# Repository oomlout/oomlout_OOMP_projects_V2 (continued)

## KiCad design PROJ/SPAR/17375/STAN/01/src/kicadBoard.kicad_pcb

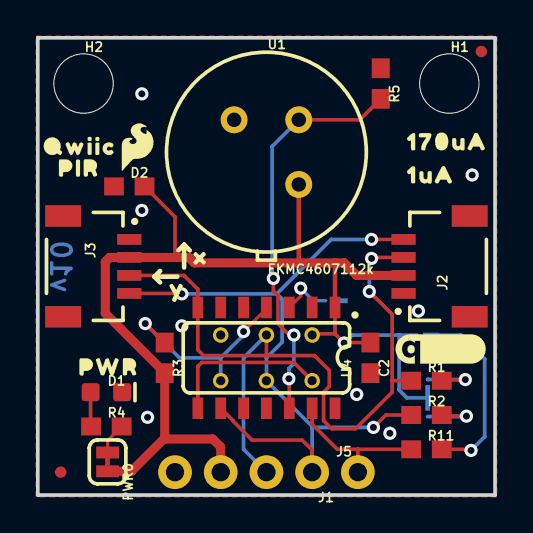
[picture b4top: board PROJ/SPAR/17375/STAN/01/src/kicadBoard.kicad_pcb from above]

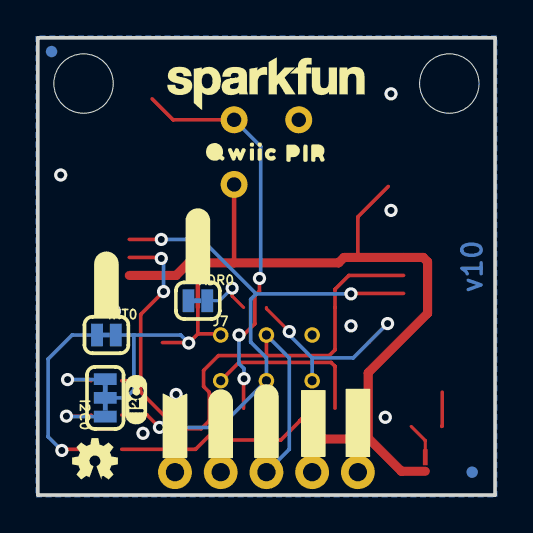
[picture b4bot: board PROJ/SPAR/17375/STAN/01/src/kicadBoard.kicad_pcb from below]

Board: 2 copper layers, 25.4 x 25.4 mm, 48 parts (18 on the bottom side), 14 nets.

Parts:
ADR0: JUMPER-SMT_2_NC_TRACE_SILK; SMT-JUMPER_2_NC_TRACE_SILK
C2: 0.1uF; 0603
D1: RED; LED-0603
D2: 24V; 0603
FRAME1: FRAME-LETTER; CREATIVE_COMMONS
H1, H2: STAND-OFF
I2C0: JUMPER-SMT_3_2-NC_TRACE_SILK; SMT-JUMPER_3_2-NC_TRACE_SILK
INT0: JUMPER-SMT_2_NC_TRACE_SILK; SMT-JUMPER_2_NC_TRACE_SILK
J1: 1X04_NO_SILK
J2, J3: QWIIC; JST04_1MM_RA
J5: 1X01_NO_SILK
J7: ISP; 2X3_TEST_POINTS
JP2, JP6, JP8, JP9: FIDUCIALUFIDUCIAL; MICRO-FIDUCIAL
LOGO1: OSHW-LOGOMINI; OSHW-LOGO-MINI
LOGO2: QWIIC_LOGO_5MM; QWIIC_5MM
LOGO3: SFE_LOGO_NAME.1_INCH; SFE_LOGO_NAME_.1
LOGO4: SFE_LOGO_FLAME.1_INCH; SFE_LOGO_FLAME_.1
PWR0: JUMPER-SMT_2_NC_TRACE_SILK; SMT-JUMPER_2_NC_TRACE_SILK
R1, R2: 2.2k; 0603
R3, R11: 10k; 0603
R4: 1k; 0603
R5: 47k; 0603
U1: EKMC4607112k; TO-3
U4: ATTINY84-ARDUINO; SO14
U$1, U$13: PIR0
U$2: 170UA0
U$3: PWR0
U$4: #INT#0
U$5: #3V3#0
U$6: #SDA#0
U$7: #SCL#0
U$8: ##INT##0
U$9: 1UA0
U$10: I_SUPER2_C-()-03
U$11: #ADR#0
U$14: X0
U$16: Y0
U$17, U$18: QWIIC0
U$19: #GND#0

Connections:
3.3V: C2.1, D2.2, I2C0.2, INT0.2, J1.3, J2.2, J3.2, J7.2, PWR0.2, R3.2, U1.VDD, U4.1
ADR0: ADR0.2, U4.3
GND: ADR0.1, C2.2, D1.C, D2.1, J1.4, J2.1, J3.1, J7.6, R5.1, U1.GND, U4.14
INT_R: INT0.1, R11.2
unnamed: D1.A, R4.1
PIR_OUT: R5.2, U1.OUT, U4.12
SCL: J1.1, J2.4, J3.4, J7.3, R2.1, U4.9
SCL_PU1: I2C0.1, R2.2
SDA: J1.2, J2.3, J3.3, J7.4, R1.1, U4.7
SDA_PU1: I2C0.3, R1.2
SDO: J7.1, U4.8
STAT: PWR0.1, R4.2
~INT: J5.1, R11.1, U4.13
~RST: J7.5, R3.1, U4.4

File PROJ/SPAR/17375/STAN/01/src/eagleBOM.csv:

"Part";"Value";"Device";"Package";"Description";"DESIGNER";"PROD_ID";"REV";"VALUE";
"ADR";"JUMPER-SMT_2_NC_TRACE_SILK";"JUMPER-SMT_2_NC_TRACE_SILK";"SMT-JUMPER_2_NC_TRACE_SILK";"Normally closed trace jumper";"";"";"";"";
"C2";"0.1uF";"0.1UF-0603-25V-(+80/-20%)";"0603";"0.1µF ceramic capacitors";"";"CAP-00810";"";"0.1uF";
"D1";"RED";"LED-RED0603";"LED-0603";"Red SMD LED";"";"DIO-00819";"";"RED";
"D2";"24V";"DIODE_TVS";"0603";"";"";"DIO-14502";"";"24V";
"FRAME1";"FRAME-LETTER";"FRAME-LETTER";"CREATIVE_COMMONS";"Schematic Frame - Letter";"";"";"";"";
"H1";"STAND-OFF";"STAND-OFF";"STAND-OFF";"Stand Off";"";"";"";"";
"H2";"STAND-OFF";"STAND-OFF";"STAND-OFF";"Stand Off";"";"";"";"";
"I2C";"JUMPER-SMT_3_2-NC_TRACE_SILK";"JUMPER-SMT_3_2-NC_TRACE_SILK";"SMT-JUMPER_3_2-NC_TRACE_SILK";"Normally closed trace jumper (2 of 2 connections)";"";"";"";"";
"INT";"JUMPER-SMT_2_NC_TRACE_SILK";"JUMPER-SMT_2_NC_TRACE_SILK";"SMT-JUMPER_2_NC_TRACE_SILK";"Normally closed trace jumper";"";"";"";"";
"J1";"";"CONN_041X04_NO_SILK";"1X04_NO_SILK";"Multi connection point. Often used as Generic Header-pin footprint for 0.1 inch spaced/style header connections";"";"CONN-09696";"";"";
"J2";"QWIIC";"QWIIC_CONNECTORJS-1MM";"JST04_1MM_RA";"SparkFun I2C Standard Qwiic Connector";"";"CONN-13694";"";"QWIIC_RIGHT_ANGLE";
"J3";"QWIIC";"QWIIC_CONNECTORJS-1MM";"JST04_1MM_RA";"SparkFun I2C Standard Qwiic Connector";"";"CONN-13694";"";"QWIIC_RIGHT_ANGLE";
"J5";"";"CONN_01PTH_NO_SILK_YES_STOP";"1X01_NO_SILK";"Single connection point. Often used as Generic Header-pin footprint for 0.1 inch spaced/style header connections";"";"";"";"";
"J7";"ISP";"AVR_SPI_PROG_3X2TESTPOINTS";"2X3_TEST_POINTS";"AVR ISP 6 Pin";"";"";"";"";
"JP2";"FIDUCIALUFIDUCIAL";"FIDUCIALUFIDUCIAL";"MICRO-FIDUCIAL";"Fiducial Alignment Points";"";"";"";"";
"JP6";"FIDUCIALUFIDUCIAL";"FIDUCIALUFIDUCIAL";"MICRO-FIDUCIAL";"Fiducial Alignment Points";"";"";"";"";
"JP8";"FIDUCIALUFIDUCIAL";"FIDUCIALUFIDUCIAL";"MICRO-FIDUCIAL";"Fiducial Alignment Points";"";"";"";"";
"JP9";"FIDUCIALUFIDUCIAL";"FIDUCIALUFIDUCIAL";"MICRO-FIDUCIAL";"Fiducial Alignment Points";"";"";"";"";
"LOGO1";"OSHW-LOGOMINI";"OSHW-LOGOMINI";"OSHW-LOGO-MINI";"Open-Source Hardware (OSHW) Logo";"";"";"";"";
"LOGO2";"QWIIC_LOGO_5MM";"QWIIC_LOGO_5MM";"QWIIC_5MM";"Qwiic Logos for placement on schematic and PCB. The 5.5mm silk logo is best for placing next to Qwiic connector.";"";"";"";"";
"LOGO3";"SFE_LOGO_NAME.1_INCH";"SFE_LOGO_NAME.1_INCH";"SFE_LOGO_NAME_.1";"SparkFun Font Logo";"";"";"";"";
"LOGO4";"SFE_LOGO_FLAME.1_INCH";"SFE_LOGO_FLAME.1_INCH";"SFE_LOGO_FLAME_.1";"SparkFun Flame Logo";"";"";"";"";
"PWR";"JUMPER-SMT_2_NC_TRACE_SILK";"JUMPER-SMT_2_NC_TRACE_SILK";"SMT-JUMPER_2_NC_TRACE_SILK";"Normally closed trace jumper";"";"";"";"";
"R1";"2.2k";"2.2KOHM-0603-1/10W-1%";"0603";"2.2kΩ resistor";"";"RES-08272";"";"2.2k";
"R2";"2.2k";"2.2KOHM-0603-1/10W-1%";"0603";"2.2kΩ resistor";"";"RES-08272";"";"2.2k";
"R3";"10k";"10KOHM-0603-1/10W-1%";"0603";"10kΩ resistor";"";"RES-00824";"";"10k";
"R4";"1k";"1KOHM-0603-1/10W-1%";"0603";"1kΩ resistor";"";"RES-07856";"";"1k";
"R5";"47k";"47KOHM-0603-1/10W-1%";"0603";"47kΩ resistor";"";"RES-07871";"";"47k";
"R11";"10k";"10KOHM-0603-1/10W-1%";"0603";"10kΩ resistor";"";"RES-00824";"";"10k";
"U1";"EKMC4607112k";"PIR_EKM4607112K";"TO-3";"Panasonic EKMCX607112 PIR Sensor";"";"IC-15368";"";"EKMC4607112k";
"U4";"ATTINY84-ARDUINO";"ATTINY84-ARDUINO";"SO14";"";"";"IC-14155";"";"";

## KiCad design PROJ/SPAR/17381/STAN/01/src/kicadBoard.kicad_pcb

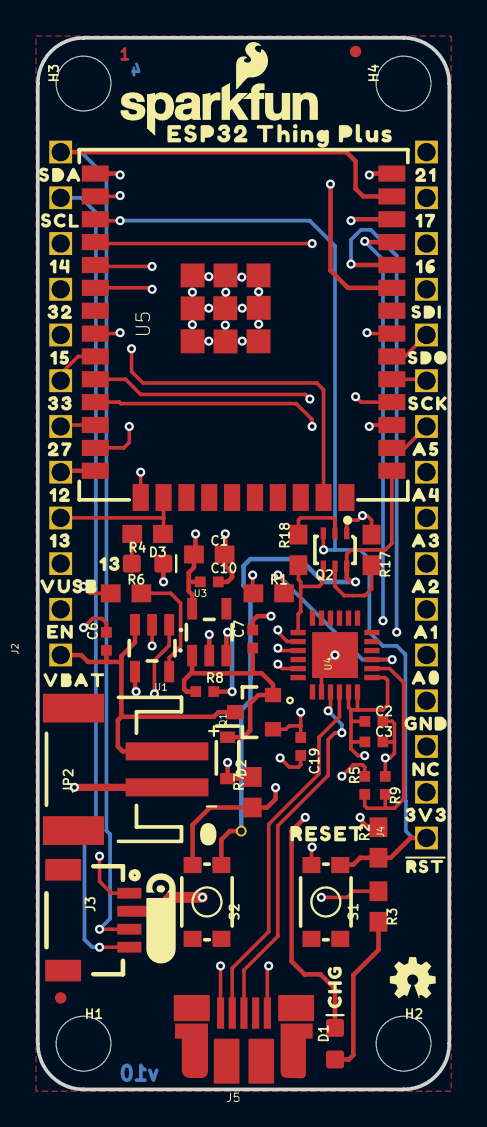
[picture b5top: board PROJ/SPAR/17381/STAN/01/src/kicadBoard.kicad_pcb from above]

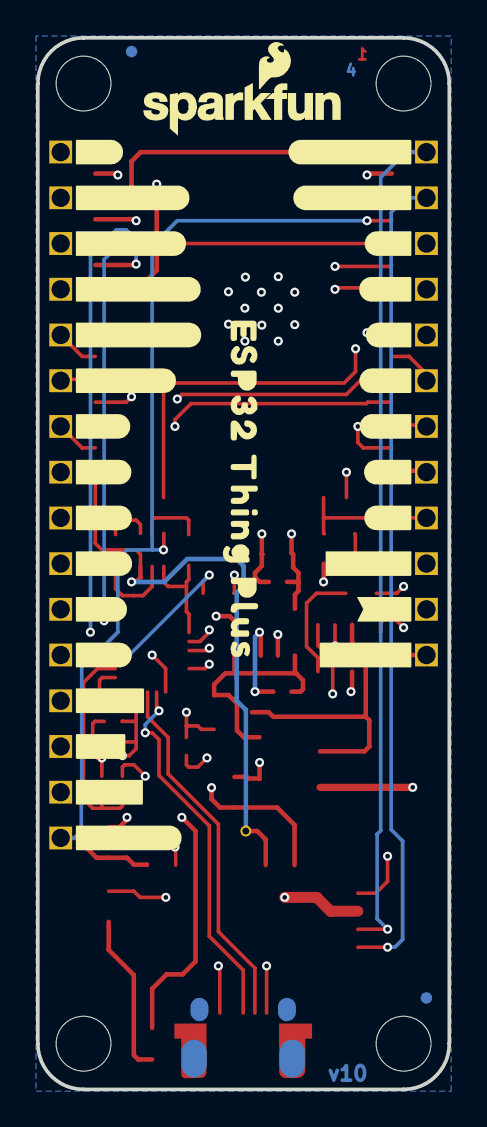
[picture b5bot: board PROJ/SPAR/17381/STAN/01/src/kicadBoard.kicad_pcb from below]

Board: 4 copper layers, 22.9 x 58.4 mm, 112 parts (32 on the bottom side), 43 nets.

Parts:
C1: 10uF; 0603
C2: 0.1uF; 0402-TIGHT
C3, C6, C19: 4.7uF; 0402-TIGHT
C7, C10: 1.0uF; 0402-TIGHT
D1: Yellow; LED-0603
D2: 1A/23V/620mV; SOD-323
D3: BLUE; LED-0603
FD1, FD2, FD3, FD4: FIDUCIALUFIDUCIAL; FIDUCIAL-MICRO
FRAME1: FRAME-LEDGER; CREATIVE_COMMONS
H1, H2, H3, H4: STAND-OFFTIGHT; STAND-OFF-TIGHT
J2: 1X12_SM_SQ_NOSILK
J3: 1X04_1MM_RA
J4: 1X16_SM_SQ_NOSILK
J5: USB-MICROB-PTH-MILL
JP2: LiPo; JST-2-SMD
LOGO2: OSHW-LOGOMINI; OSHW-LOGO-MINI
LOGO3, LOGO5: SFE_LOGO_NAME_FLAME.1_INCH; SFE_LOGO_NAME_FLAME_.1
LOGO4: FOUR_LAYER_WARNING
LOGO6: QWIIC_LOGO_5MM; QWIIC_5MM
Q1: 2.5A/30V; SOT23-3@1
Q2: MBT3904DW1T1; SC70-6
R1, R2, R7, R17, R18: 10k; 0603
R3: 1K; 0603
R4: 1k; 0603
R5: 22k; 0402-TIGHT
R6: 2.0k; 0603
R8: 100k; 0402-TIGHT
R9: 33k; 0402-TIGHT
S1: RESET; TACTILE_SWITCH_SMD_4.6X2.8MM
S2: 0; TACTILE_SWITCH_SMD_4.6X2.8MM
TP1: TP_15TH
U1: MCP73831; SOT23-5
U3: AP2112K-3.3V; SOT23-5
U4: CP210X; QFN24
U5: ESP-WROOM-32EU; ESP-WROOM-32EU-NARROW
U$1: ESP32_THING_PLUS_0
U$2: SDI0
U$3: #21#0
U$4: #17#TX1#0
U$5: #16#RX1#0
U$6: SDO0
U$7: #RST#0
U$8: #19#CIPO#0
U$10: #18#COPI#0
U$11: #5#SCK#0
U$12: #A5#0
U$19: #A4#0
U$21: #A3#0
U$22: #A2#0
U$24: ESP32_THING_PLUS0
U$25: SDA0
U$26: SCL0
U$27: #A1#0
U$28: #A0#0
U$31: #23#SDA#0
U$32: #GND#0
U$33: #22#SCL#0
U$34: #14#0
U$35: #32#0
U$36: #15#0
U$37: #33#0
U$38: #27#0
U$39: #12#0
U$40: #13#0
U$41: #VUSB#0
U$42: #VBAT#0
U$43: #EN#0
U$44: #NC#0
U$45: #3V3#0
U$46: ##RESET##0
U$58: 140
U$59: ORDERING_INSTRUCTIONS
U$68: 320
U$69: 150
U$70: 330
U$71: 270
U$72: 120
U$73, U$74: 130
U$75: VUSB0
U$76: EN0
U$77: VBAT0
U$78: CHG0
U$79: RESET0
U$81: 3V30
U$82: NC0
U$83: GND0
U$84: A00
U$85: A10
U$86: A20
U$87: A30
U$88: A40
U$89: A50
U$90: SCK0
U$93: 160
U$94: 170
U$95: 210
U$96: 00

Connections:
0: Q2.6, S2.4, TP1.P$1, U5.25
3.3V: C1.1, C2.1, C3.1, C10.1, J3.2, J4.2, R1.1, R2.2, U3.5, U4.5, U4.6, U4.7, U5.2
12: J2.5, U5.14
13: J2.4, R4.1, U5.16
14: J2.10, U5.13
15: J2.8, U5.23
16: J4.14, U5.27
17: J4.15, U5.28
21: J4.16, U5.33
27: J2.6, U5.12
32: J2.9, U5.8
33: J2.7, U5.9
A0: J4.5, U5.11
A1: J4.6, U5.10
A2: J4.7, U5.6
A3: J4.8, U5.5
A4: J4.9, U5.4
A5: J4.10, U5.26
CHG: D1.C, U1.1
CHIP_PU: J4.1, Q2.3, R2.1, S1.4, U5.3
CIPO: J4.13, U5.31
COPI: J4.12, U5.30
D+: J5.D+, U4.3
D-: J5.D-, U4.4
DTR: Q2.1, R17.1, U4.23
EN: J2.2, R8.2, U3.3
GND: C1.2, C2.2, C3.2, C6.2, C7.2, C10.2, C19.2, D3.C, J3.1, J4.4, J5.GND, JP2.1, R6.1, R7.1, R9.1, S1.1, S2.1, U1.2, U3.2, U4.2, U4.PAD, U5.1, U5.15, U5.38, U5.GND, U5.P$1, U5.P$2, U5.P$3, U5.P$4, U5.P$5, U5.P$6, U5.P$7, U5.P$8
unnamed: R1.2, U4.9
unnamed: D3.A, R4.2
unnamed: R5.1, R9.2, U4.8
unnamed: Q2.5, R17.2
unnamed: Q2.2, R18.2
unnamed: R6.2, U1.5
unnamed: D1.A, R3.2
RTS: Q2.4, R18.1, U4.19
RX: U4.20, U5.35
SCK: J4.11, U5.29
SCL: J2.11, J3.4, U5.36
SDA: J2.12, J3.3, U5.37
TX: U4.21, U5.34
VIN: C7.1, D2.C, Q1.2, R8.1, U3.1
V_BATT: C6.1, J2.1, JP2.2, Q1.3, U1.3
V_USB: C19.1, D2.A, J2.3, J5.VBUS, Q1.1, R3.1, R5.2, R7.2, U1.4

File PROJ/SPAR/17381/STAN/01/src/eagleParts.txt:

Partlist

Exported from boardEagle.brd at 20/08/2022 18:28

EAGLE Version 9.6.2 Copyright (c) 1988-2020 Autodesk, Inc.

Assembly variant: 

Part     Value             Package                      Library               Position (inch)       Orientation

C1       10uF              0603                         SparkFun-Capacitors   (0.375 1.17)          R0
C2       0.1uF             0402-TIGHT                   SparkFun-Capacitors   (0.735 0.805)         R0
C3       4.7uF             0402-TIGHT                   SparkFun-Capacitors   (0.735 0.76)          R0
C6       4.7uF             0402-TIGHT                   SparkFun-Capacitors   (0.15 0.98)           R90
C7       1.0uF             0402-TIGHT                   SparkFun-Capacitors   (0.47 0.985)          R90
C10      1.0uF             0402-TIGHT                   SparkFun-Capacitors   (0.375 1.11)          R0
C19      4.7uF             0402-TIGHT                   SparkFun-Capacitors   (0.575 0.75)          R270
D1       Yellow            LED-0603                     SparkFun-LED          (0.65 0.1)            R90
D2       1A/23V/620mV      SOD-323                      SparkFun-DiscreteSemi (0.415 0.725)         R270
D3       BLUE              LED-0603                     SparkFun-LED          (0.24 1.15)           R0
FD1      FIDUCIALUFIDUCIAL FIDUCIAL-MICRO               SparkFun-Aesthetics   (0.695 2.27)          R0
FD2      FIDUCIALUFIDUCIAL FIDUCIAL-MICRO               SparkFun-Aesthetics   (0.695 2.27)          MR0
FD3      FIDUCIALUFIDUCIAL FIDUCIAL-MICRO               SparkFun-Aesthetics   (0.05 0.2)            R0
FD4      FIDUCIALUFIDUCIAL FIDUCIAL-MICRO               SparkFun-Aesthetics   (0.05 0.2)            MR0
J2                         1X12_SM_SQ_NOSILK            SparkFun-Connectors   (0.05 0.95)           R90
J3                         1X04_1MM_RA                  SparkFun-Connectors   (0.2 0.37)            R270
J4                         1X16_SM_SQ_NOSILK            SparkFun-Connectors   (0.85 0.55)           R90
J5                         USB-MICROB-PTH-MILL          SparkFun-Connectors   (0.45082677 0.167)    R0
JP2      LiPo              JST-2-SMD                    SparkFun-Connectors   (0.137 0.7)           R90
Q1       2.5A/30V          SOT23-3@1                    SparkFun-DiscreteSemi (0.475 0.825)         R90
Q2       MBT3904DW1T1      SC70-6                       SparkFun-DiscreteSemi (0.65 1.18)           R180
R1       10k               0603                         SparkFun-Resistors    (0.505 1.085)         R0
R2       10k               0603                         SparkFun-Resistors    (0.745 0.54)          R90
R3       1K                0603                         SparkFun-Resistors    (0.745 0.4)           R270
R4       1k                0603                         SparkFun-Resistors    (0.24 1.215)          R180
R5       22k               0402-TIGHT                   SparkFun-Resistors    (0.715 0.665)         R90
R6       2.0k              0603                         SparkFun-Resistors    (0.193 1.085)         R0
R7       10k               0603                         SparkFun-Resistors    (0.47 0.65)           R90
R8       100k              0402-TIGHT                   SparkFun-Resistors    (0.365 0.87)          R0
R9       33k               0402-TIGHT                   SparkFun-Resistors    (0.76 0.665)          R270
R17      10k               0603                         SparkFun-Resistors    (0.73 1.18)           R270
R18      10k               0603                         SparkFun-Resistors    (0.57 1.18)           R90
S1       RESET             TACTILE_SWITCH_SMD_4.6X2.8MM SparkFun-Switches     (0.63 0.41)           R270
S2       0                 TACTILE_SWITCH_SMD_4.6X2.8MM SparkFun-Switches     (0.37 0.41)           R270
TP1                        TP_15TH                      SparkFun-Connectors   (0.445 0.565)         R0
U1       MCP73831          SOT23-5                      SparkFun-PowerIC      (0.25 0.965)          R180
U3       AP2112K-3.3V      SOT23-5                      SparkFun-PowerIC      (0.375 1)             R0
U4       CP210X            QFN24                        SparkFun-IC-Comms     (0.65 0.95)           R90
U5       ESP-WROOM-32EU    ESP-WROOM-32EU-NARROW        esp-wroom-32u         (0.45 1.75)           R90

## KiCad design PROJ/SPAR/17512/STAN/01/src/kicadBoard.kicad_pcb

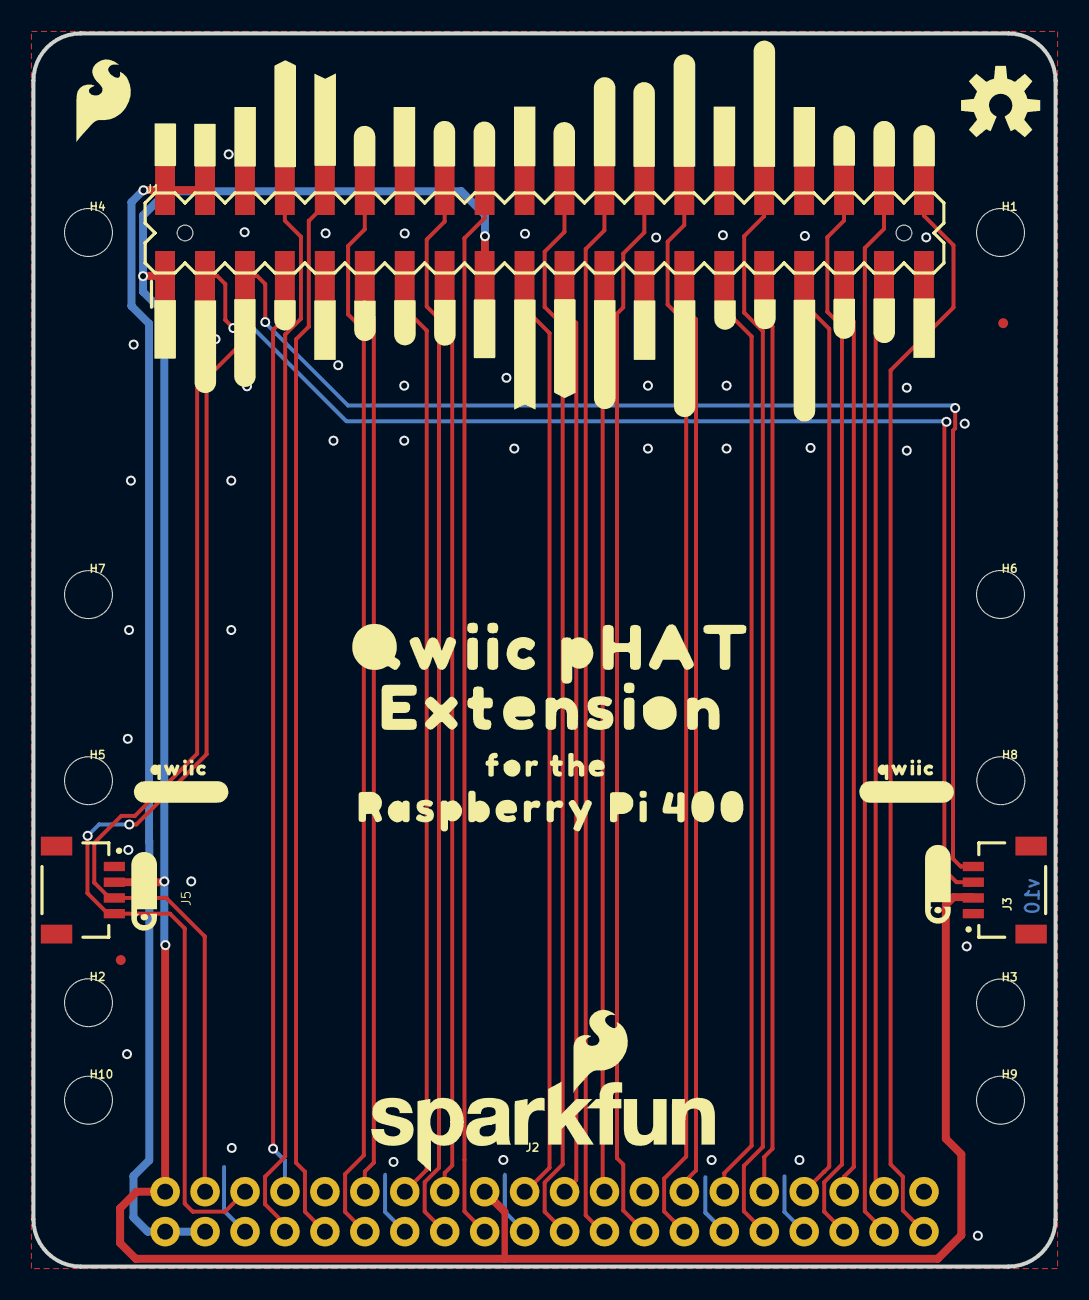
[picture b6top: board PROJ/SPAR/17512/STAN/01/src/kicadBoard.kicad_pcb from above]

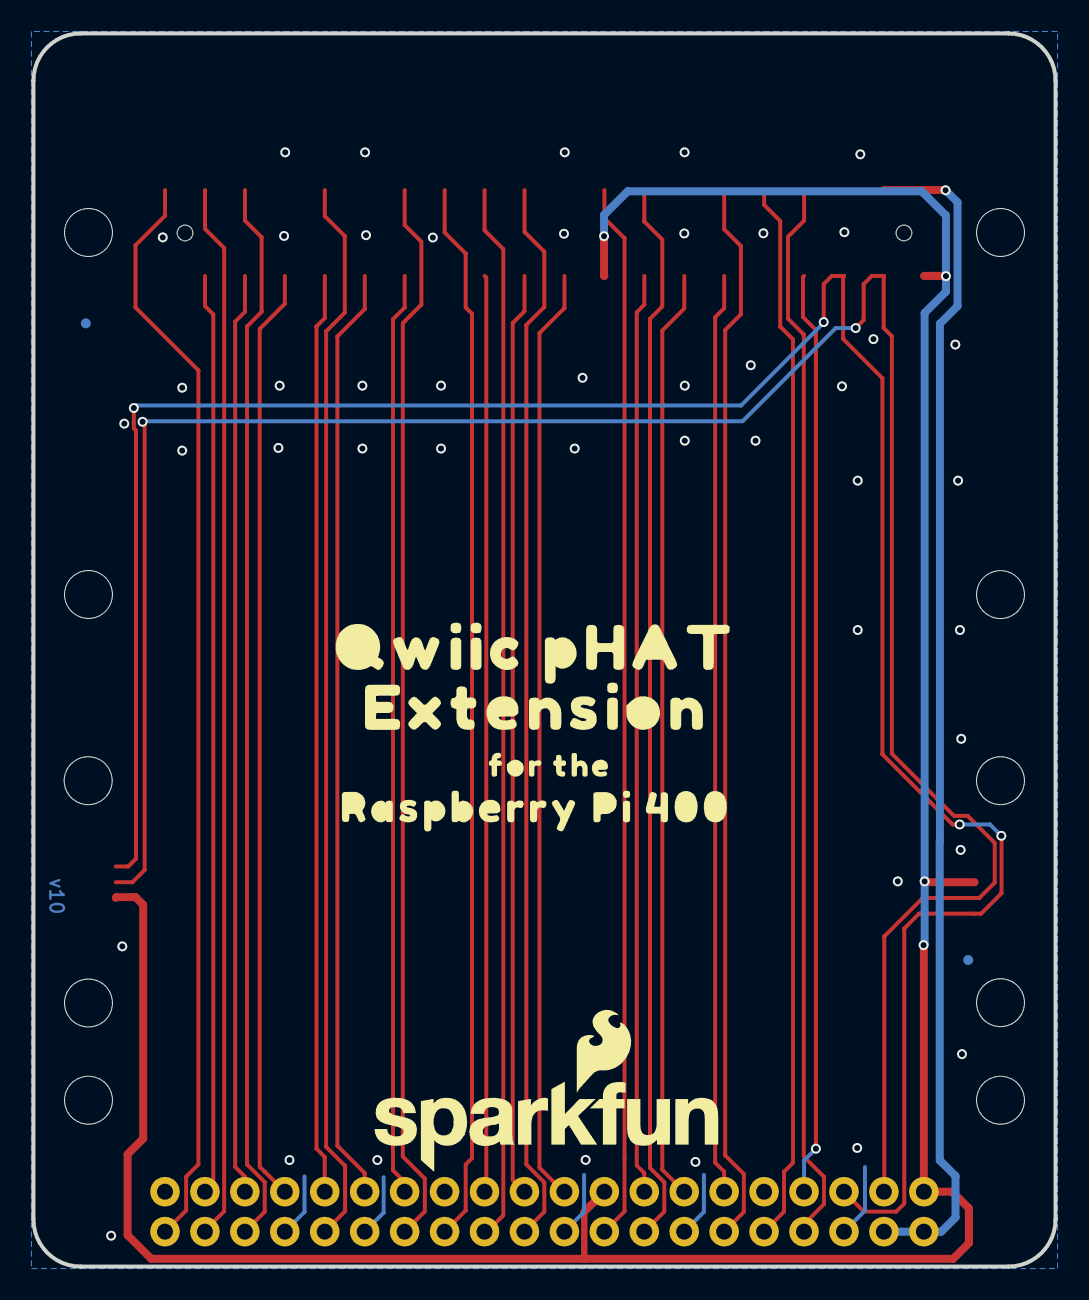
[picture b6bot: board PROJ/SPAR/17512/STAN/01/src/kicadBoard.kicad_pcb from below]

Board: 2 copper layers, 65.0 x 78.4 mm, 77 parts (7 on the bottom side), 31 nets.

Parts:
FD1, FD2, FD3, FD4: FIDUCIALUFIDUCIAL; FIDUCIAL-MICRO
FRAME1: FRAME-LETTER; CREATIVE_COMMONS
H1, H2, H3, H4, H5, H6, H7, H8, H9, H10: STAND-OFFTIGHT; STAND-OFF-TIGHT
J1: RASPBERRYPI-40-PIN-GPIO_SMD_MALE; RASPBERRY_PI_HAT_40_PIN_SMD_MALE
J2: RASPBERRYPI-40-PIN-GPIO_RIGHT_ANGLE; 2X20_RIGHT_ANGLE
J3, J5: QWIIC_RIGHT_ANGLE; JST04_1MM_RA
LOGO1, LOGO4: QWIIC_LOGO_5MM; QWIIC_5MM
LOGO2, LOGO5: SFE_LOGO_NAME_FLAME.2_INCH; SFE_LOGO_NAME_FLAME_.2
LOGO3: OSHW-LOGOM; OSHW-LOGO-M
U$1: #SDA#2#4
U$2: #SCL#3#4
U$3, U$13: FOR_THE40034
U$4, U$5: #3V3#0
U$6: #4#4
U$7: #5#28
U$8, U$9: #5V#28
U$10: #6#28
U$11: #7#CE1#29
U$12: #8#CE0#29
U$14: #SCLK#11#28
U$15: #ID_SD#0#28
U$16: #12#PWM0#29
U$17: #PWM1#13#28
U$18: #14#TXO#29
U$19: #15#RXI#29
U$20: #16#29
U$21: #17#5
U$22: #18#29
U$23: #19#28
U$24: #20#29
U$25: #21#29
U$26: #22#28
U$27: #23#29
U$28: #24#29
U$29: #25#29
U$30: #26#28
U$31: #27#18
U$32, U$33, U$34, U$35, U$36, U$37, U$38, U$39: #GND#28
U$40: #1#ID_SC#29
U$51: #CIPO#9#28
U$52: #COPI#10#28
U$75, U$89: QWIIC_PHAT31
U$76, U$90: EXTENSION32
U$81: SFE_LOGO_FLAME_.2
U$82, U$83: #MOUNT#29
U$84, U$85: QWIIC30
U$86, U$91: RASPBERRY_PI_40033

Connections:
0/ID_SD: J1.27, J2.27
1/ID_SC: J1.28, J2.28
2/SDA: J1.3, J2.3, J3.3, J5.3
3.3V: J1.1, J1.17, J2.1, J2.17, J3.2, J5.2
3/SCL: J1.5, J2.5, J3.4, J5.4
5V: J1.2, J1.4, J2.2, J2.4
7/CE1: J1.26, J2.26
8/CE0: J1.24, J2.24
9/CIPO: J1.21, J2.21
10/COPI: J1.19, J2.19
11/SCLK: J1.23, J2.23
12/PWM0: J1.32, J2.32
13/PWM1: J1.33, J2.33
14/TXO: J1.8, J2.8
15/RXI: J1.10, J2.10
18/PCM_CLK: J1.12, J2.12
19/PCM_FS: J1.35, J2.35
20/PCM_DIN: J1.38, J2.38
21/PCM_DOUT: J1.40, J2.40
GND: J1.6, J1.9, J1.14, J1.20, J1.25, J1.30, J1.34, J1.39, J2.6, J2.9, J2.14, J2.20, J2.25, J2.30, J2.34, J2.39, J3.1, J5.1
GP4: J1.7, J2.7
GP5: J1.29, J2.29
GP6: J1.31, J2.31
GP16: J1.36, J2.36
GP17: J1.11, J2.11
GP22: J1.15, J2.15
GP23: J1.16, J2.16
GP24: J1.18, J2.18
GP25: J1.22, J2.22
GP26: J1.37, J2.37
GP27: J1.13, J2.13

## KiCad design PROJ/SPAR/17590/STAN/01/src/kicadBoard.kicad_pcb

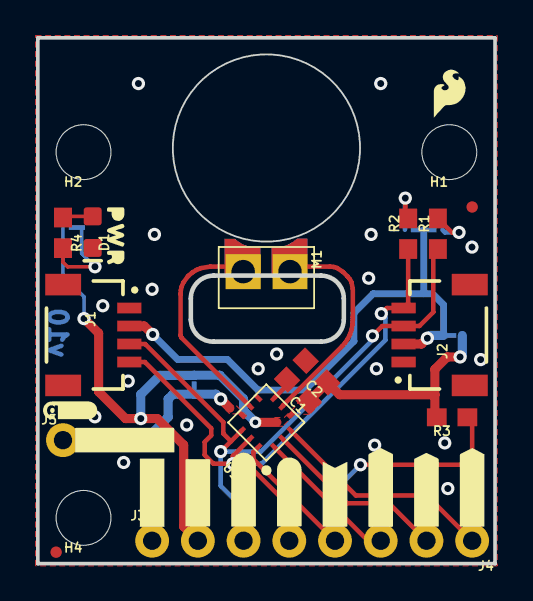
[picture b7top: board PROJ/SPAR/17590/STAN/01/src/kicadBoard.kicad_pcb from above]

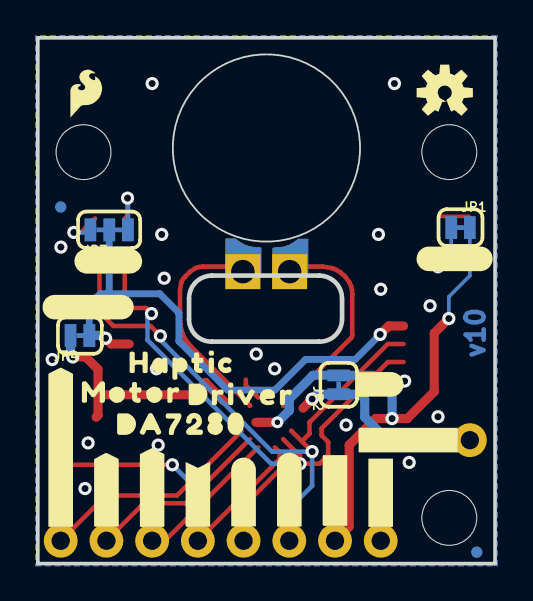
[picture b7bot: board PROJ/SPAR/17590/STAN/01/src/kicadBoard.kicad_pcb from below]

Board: 2 copper layers, 25.4 x 29.2 mm, 58 parts (25 on the bottom side), 16 nets.

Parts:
C1: 0.1uF; 0603
C2: 4.7uF; 0603
D1: RED; LED-0603
FD1, FD2, FD3, FD4: FIDUCIALUFIDUCIAL; FIDUCIAL-MICRO
FRAME1: FRAME-LETTER; CREATIVE_COMMONS
H1, H2, H4: STAND-OFFTIGHT; STAND-OFF-TIGHT
J1, J2: QWIIC_RIGHT_ANGLE; JST04_1MM_RA
J3, J4: 1X04_NO_SILK
J5: 1X01_NO_SILK
JP1, JP2, JP4: LED; SMT-JUMPER_2_NC_TRACE_SILK
JP3: I2C_PU; SMT-JUMPER_3_2-NC_TRACE_SILK
LOGO1: SPECIAL_INSTRUCTIONS-ORDERING; ORDERING_INSTRUCTIONS
LOGO2: OSHW-LOGOS; OSHW-LOGO-S
LOGO4: SFE_LOGO_FLAME.1_INCH; SFE_LOGO_FLAME_.1
M1: G1040003D_LRA_CASTELLATED; COIN_VIBRATION_MOTOR_CASTEL
R1, R2: 4.7k; 0603
R3: 10k; 0603
R4: 1k; 0603
U1: HAPTIC_DRIVER_DA7280; QFN_DA7280
U$1: QWIIC_LOGO_3MM; QWIIC_3MM
U$2: #3V3#1
U$3, U$18: #GND#0
U$4: #GPI0#6
U$5: #GPI1#6
U$6: #GPI2#6
U$7: #VDD#4
U$8: #SDA#4
U$9: HAPTIC6
U$10: MOTOR7
U$11: DRIVER8
U$12: #GPI0#PWM#2
U$13: #GPI1#2
U$14: #GPI2#2
U$15, U$25: #VDDIO#5
U$16: #SDA#0
U$19: #SCL#5
U$20: PWR72810
U$21: #SCL#1
U$23: #I2C#4
U$24: #LED#4
U$26: SFE_LOGO_FLAME_.1
U$27: ##INT##3
U$28: ##INT##6
U$29: DA72809
U$30: #IO#6
U$31: #QISO#0

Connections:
GND: C1.2, C2.2, D1.C, J1.1, J2.1, J3.1, U1.P6, U1.P7
GPI0/PWM: J4.1, U1.P3
GPI1: J4.2, U1.P2
GPI2: J4.3, U1.P1
unnamed: D1.A, R4.1
unnamed: JP1.1, R4.2
unnamed: JP3.3, R1.2
unnamed: JP3.1, R2.2
unnamed: M1.P$1, U1.P5
unnamed: M1.P$2, U1.P8
QWIIC_BUS: J1.2, J2.2, JP3.2, JP4.1
SCL: J1.4, J2.4, J3.4, R2.1, U1.P11
SDA: J1.3, J2.3, J3.3, R1.1, U1.P10
VDD: C1.1, C2.1, J3.2, JP1.2, JP2.2, JP4.2, R3.2, U1.P4
VDDIO: J5.1, JP2.1, U1.P9
~INT: J4.4, R3.1, U1.P12

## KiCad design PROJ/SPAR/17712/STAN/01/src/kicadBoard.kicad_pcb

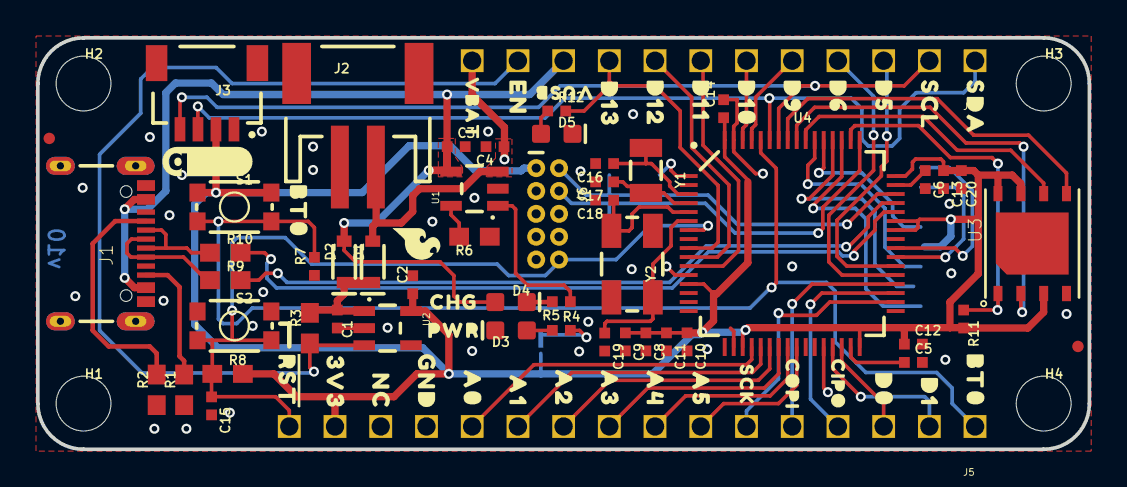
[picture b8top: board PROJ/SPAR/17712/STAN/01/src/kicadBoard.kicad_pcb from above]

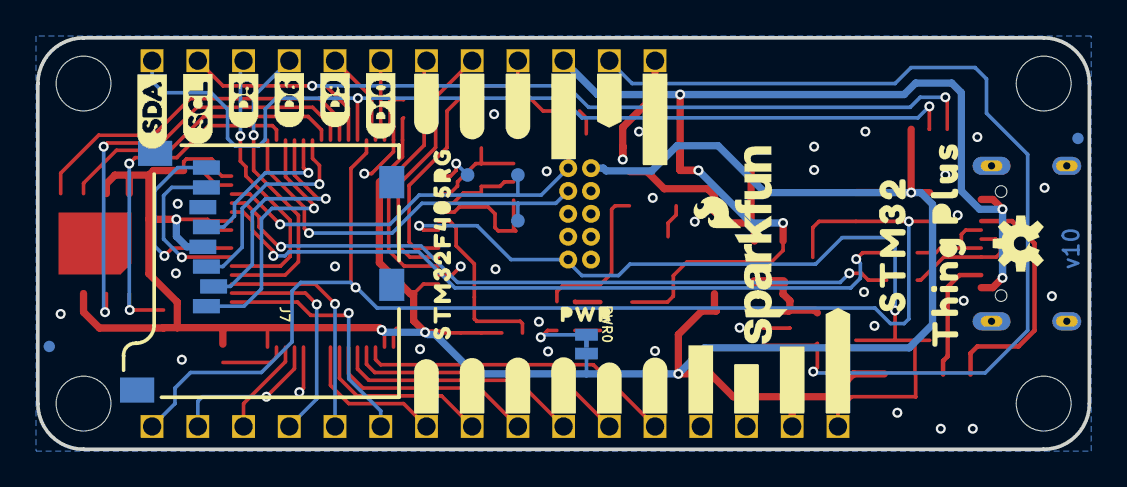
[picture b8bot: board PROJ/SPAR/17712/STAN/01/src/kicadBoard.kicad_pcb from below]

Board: 2 copper layers, 58.4 x 22.9 mm, 125 parts (35 on the bottom side), 59 nets.

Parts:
C1, C2, C9: 1.0uF; 0402-TIGHT
C3, C4, C10: 4.7uF; 0402-TIGHT
C5, C6: 2.2uF; 0402-TIGHT
C8, C11, C12, C13, C14, C15, C20: 0.1uF; 0402-TIGHT
C16, C17: 15pF; 0402-TIGHT
C18, C19: 22pF; 0402-TIGHT
D1, D2: 3A/10V/280mV; SOD-323
D3: RED; LED-0603
D4: Yellow; LED-0603
D5: BLUE; LED-0603
FD1, FD2, FD3, FD4: FIDUCIALUFIDUCIAL; FIDUCIAL-MICRO
FRAME1: FRAME-LETTER; CREATIVE_COMMONS
H1, H2, H3, H4: STAND-OFFTIGHT; STAND-OFF-TIGHT
J1: USB-C-16P-2LAYER-PADS
J2: JST-2-SMD
J3: QWIIC_RA; JST04_1MM_RA
J4: 1X12_SM_SQ_NOSILK
J5: 1X16_SM_SQ_NOSILK
J6: CORTEX_DEBUG; 2X5-PTH-1.27MM-NO_SILK
J7: MICRO-SD; MICRO-SD-SOCKET
LOGO1: QWIIC_LOGO_5MM; QWIIC_5MM
LOGO2: SFE_LOGO_NAME_FLAME.1_INCH; SFE_LOGO_NAME_FLAME_.1
LOGO3: OSHW-LOGOS; OSHW-LOGO-S
PWR0: SMT-JUMPER_2_NC_TRACE_NO-SILK
R1, R2: 5.1k; 0603
R3: 10k; 0603
R4, R5, R12: 1k; 0402-TIGHT
R6: 2.0k; 0603
R7, R11: 100k; 0402-TIGHT
R8: 4.7k; 0603
R9, R10: 22; 0603
S1, S2: TACTILE_SWITCH_SMD_4.6X2.8MM
TP1, TP2: PAD.03X.03
U1: MCP73831; SOT23-5
U2: 3.3V; SOT23-5
U3: W25QXX128MBIT-6X5; WSON-8-6X5
U4: STM32F405RGT6; TQFP64
U$1: D53
U$2: #RST#0
U$3, U$49: BT00
U$4: D130
U$5, U$58: PWR0
U$6: CHG0
U$7: ##RESET##0
U$8: #3V3#0
U$9: #NC#0
U$10: #GND#0
U$11: #A0#0
U$12: #A1#0
U$13: #A2#0
U$14: #A3#0
U$15: #A4#0
U$16: #A5#0
U$23: D62
U$24: D91
U$25, U$55: D100
U$26: SCL4
U$27: SDA5
U$29: #D11#0
U$30: #D12#0
U$31: #D13#0
U$32: #VUSB#0
U$33: #EN#0
U$34: #VBAT#0
U$35: 3V30
U$36: NC0
U$37: GND0
U$38: A00
U$39: A10
U$40: A20
U$41: A30
U$42: A40
U$43: A50
U$44: SCK0
U$45: COPI0
U$46: CIPO0
U$47: D00
U$48: D10
U$50: VBAT_0
U$51: EN_0
U$52: D50
U$53: D60
U$54: D90
U$56: D110
U$57: D120
U$59: SCL_0
U$60: SDA_0
U$61: VUSB0
U$62: STM320
U$63: THING_PLUS0
U$64: STM32F405RG0
U$65: SFE_LOGO_FLAME_.1
VB0: PAD.03X.03
Y1: 32.768kHz; CRYSTAL-SMD-3.2X1.5MM
Y2: 12MHz; CRYSTAL-SMD-5X3.2-4PAD

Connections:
3.3V: C2.1, C8.1, C9.1, C10.1, C11.1, C12.1, C13.1, C14.1, C20.1, J3.2, J5.15, J6.1, J7.VCC, PWR0.2, R8.2, R11.2, S1.3, S1.4, U2.5, U3.3, U3.7, U3.8, U4.13, U4.19, U4.32, U4.42, U4.43, U4.48, U4.64
32KHZ_IN: C16.1, U4.3, Y1.P$1
32KHZ_OUT: C17.1, U4.4, Y1.P$2
A0: J5.12, U4.20
A1: J5.11, U4.21
A2: J5.10, U4.22
A3: J5.9, U4.23
A4: J5.8, U4.24
A5: J5.7, U4.25
BOOT0: J5.1, R7.2, S1.1, S1.2, U4.60
CIPO: J5.4, U4.35
COPI: J5.5, U4.36
D0/RX: J5.3, U4.30
D1/TX: J5.2, U4.29
D5: J4.3, U4.38
D6: J4.4, U4.37
D9: J4.5, U4.61
D10: J4.6, U4.62
D11: J4.7, U4.11
D12: J4.8, U4.10
D13: J4.9, R12.2, U4.9
D+: R9.2, U4.45
D-: R10.2, U4.44
EN: J4.11, R3.1, U2.3
FLASH_SCK: U3.6, U4.55
FLASH_SDI: U3.5, U4.57
FLASH_SDO: U3.2, U4.56
FLASH_~CS: R11.1, U3.1, U4.50
GND: C1.2, C2.2, C3.2, C4.2, C5.2, C6.2, C8.2, C9.2, C10.2, C11.2, C12.2, C13.2, C14.2, C15.2, C16.2, C17.2, C18.2, C19.2, C20.2, D3.C, D5.C, J1.GND, J1.GND2, J1.SHLD1, J1.SHLD2, J1.SHLD3, J1.SHLD4, J2.1, J3.1, J5.13, J6.3, J6.5, J6.9, J7.CD1, J7.GND, J7.GND1, J7.GND3, R1.1, R2.1, R6.1, R7.1, S2.3, S2.4, U1.2, U2.2, U3.4, U4.12, U4.18, U4.28, U4.63
unnamed: D5.A, R12.1
unnamed: PWR0.1, R4.2
unnamed: J1.A6, J1.B6, R9.1
unnamed: J1.A7, J1.B7, R10.1
unnamed: D3.A, R4.1
unnamed: R6.2, U1.5
unnamed: J1.A5, R2.2
unnamed: J1.B5, R1.2
unnamed: D4.C, R5.2
unnamed: R5.1, U1.1
unnamed: C5.1, U4.31
unnamed: C6.1, U4.47
OSC_IN: C18.1, U4.5, Y2.1
OSC_OUT: C19.1, U4.6, Y2.3
SCK: J5.6, U4.34
SCL: J3.4, J4.2, U4.58
SDA: J3.3, J4.1, U4.59
SDIO_CLK: J7.SCLK, U4.53
SDIO_CMD: J7.DI/CMD, U4.54
SDIO_D0: J7.DO/DAT0, U4.39
SDIO_D1: J7.DAT1, U4.40
SDIO_D2: J7.DAT2, U4.51
SDIO_D3: J7.CS/DAT3, U4.52
SWCLK: J6.4, TP2.P$1, U4.49
SWDIO: J6.2, TP1.P$1, U4.46
VB: U4.1, VB0.P$1
VIN: C1.1, D1.C, D2.C, R3.2, U2.1
V_BATT: C4.1, D1.A, J2.2, J4.12, U1.3
V_USB: C3.1, D2.A, D4.A, J1.VBUS1, J1.VBUS2, J4.10, U1.4
~RESET: C15.1, J5.16, J6.10, R8.1, S2.1, S2.2, U4.7
